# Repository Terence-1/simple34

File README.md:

# simple34
34 key choc split keyboard. hotswapable. revisible pcb

guys i don't know how to use git but i am learning

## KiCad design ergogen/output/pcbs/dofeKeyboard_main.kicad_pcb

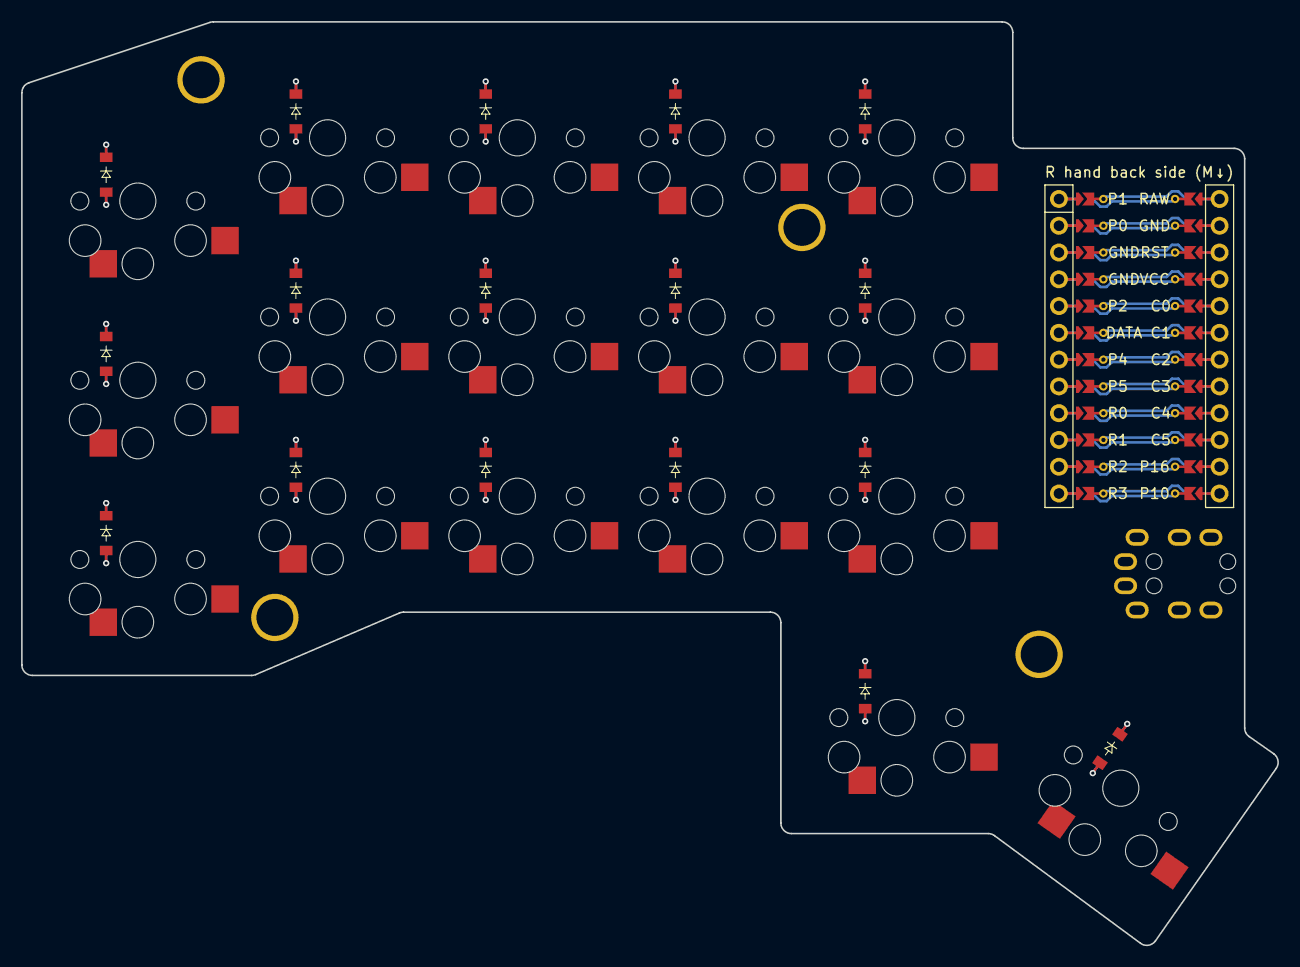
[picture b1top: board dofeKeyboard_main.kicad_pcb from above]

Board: 2 copper layers, 119.2 x 87.6 mm, 40 parts (0 on the bottom side), 30 nets.

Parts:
D1, D2, D3, D4, D5, D6, D7, D8, D9, D10, D11, D12, D13, D14, D15, D16, D17: diode_tht_sod123
H1, H2, H3, H4: mounting_hole_plated
MCU1: mcu_supermini_nrf52840
S1, S2, S3, S4, S5, S6, S7, S8, S9, S10, S11, S12, S13, S14, S15, S16, S17: PG1350
TRRS1: TRRS-PJ-320A-dual

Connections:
C0: MCU1.105, S1.2, S2.2, S3.2
C1: MCU1.106, S4.2, S5.2, S6.2
C2: MCU1.107, S7.2, S8.2, S9.2
C3: MCU1.108, S10.2, S11.2, S12.2
C4: MCU1.109, S13.2, S14.2, S15.2, S16.2
C5: MCU1.110, S17.2
DATA: MCU1.119, TRRS1.2
GND: MCU1.102, MCU1.121, MCU1.122, TRRS1.3
R0: D3.1, D6.1, D9.1, D12.1, D15.1, MCU1.116
R1: D2.1, D5.1, D8.1, D11.1, D14.1, MCU1.115
R2: D1.1, D4.1, D7.1, D10.1, D13.1, MCU1.114
R3: D16.1, D17.1, MCU1.113
VCC: MCU1.104, TRRS1.1
index_bottom: D10.2, S10.1
index_home: D11.2, S11.1
index_top: D12.2, S12.1
inner_bottom: D13.2, S13.1
inner_home: D14.2, S14.1
inner_top: D15.2, S15.1
left_cluster: D16.2, S16.1
middle_bottom: D7.2, S7.1
middle_home: D8.2, S8.1
middle_top: D9.2, S9.1
pinky_bottom: D1.2, S1.1
pinky_home: D2.2, S2.1
pinky_top: D3.2, S3.1
right_cluster: D17.2, S17.1
ring_bottom: D4.2, S4.1
ring_home: D5.2, S5.1
ring_top: D6.2, S6.1

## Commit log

2025-11-17 just an image
2025-11-17 move my image
2025-11-17 just a few thing + image
2025-12-06 Add image to README for myKeyboard
    Added an image to the README for visual reference.
2025-12-06 it think this is a good build guide
2025-12-06 more updates
2025-12-07 v1 qmk
2025-12-07 update build guide
2025-12-07 update vial thing
2025-12-07 update v1 qmk
2026-01-23 Initial plan
2026-01-23 update zmk files
2026-01-23 updade zmk files
2026-01-27 update zmk
2026-01-27 update zmk file
2026-01-28 Add image
2026-02-04 repo rename
2026-02-04 match name to repo
2026-02-04 match names to repo
2026-03-13 rename folder
2026-03-20 add 3d cases
2026-03-20 add 0.8mm to top plate
2026-04-04 Remove 3D case definitions and output files
2026-04-04 Remove unused case-related outlines
2026-04-14 added 'foam' pcb
2026-05-01 added rmk config
2026-05-05 move qmk to own repo
2026-05-05 zmk again
